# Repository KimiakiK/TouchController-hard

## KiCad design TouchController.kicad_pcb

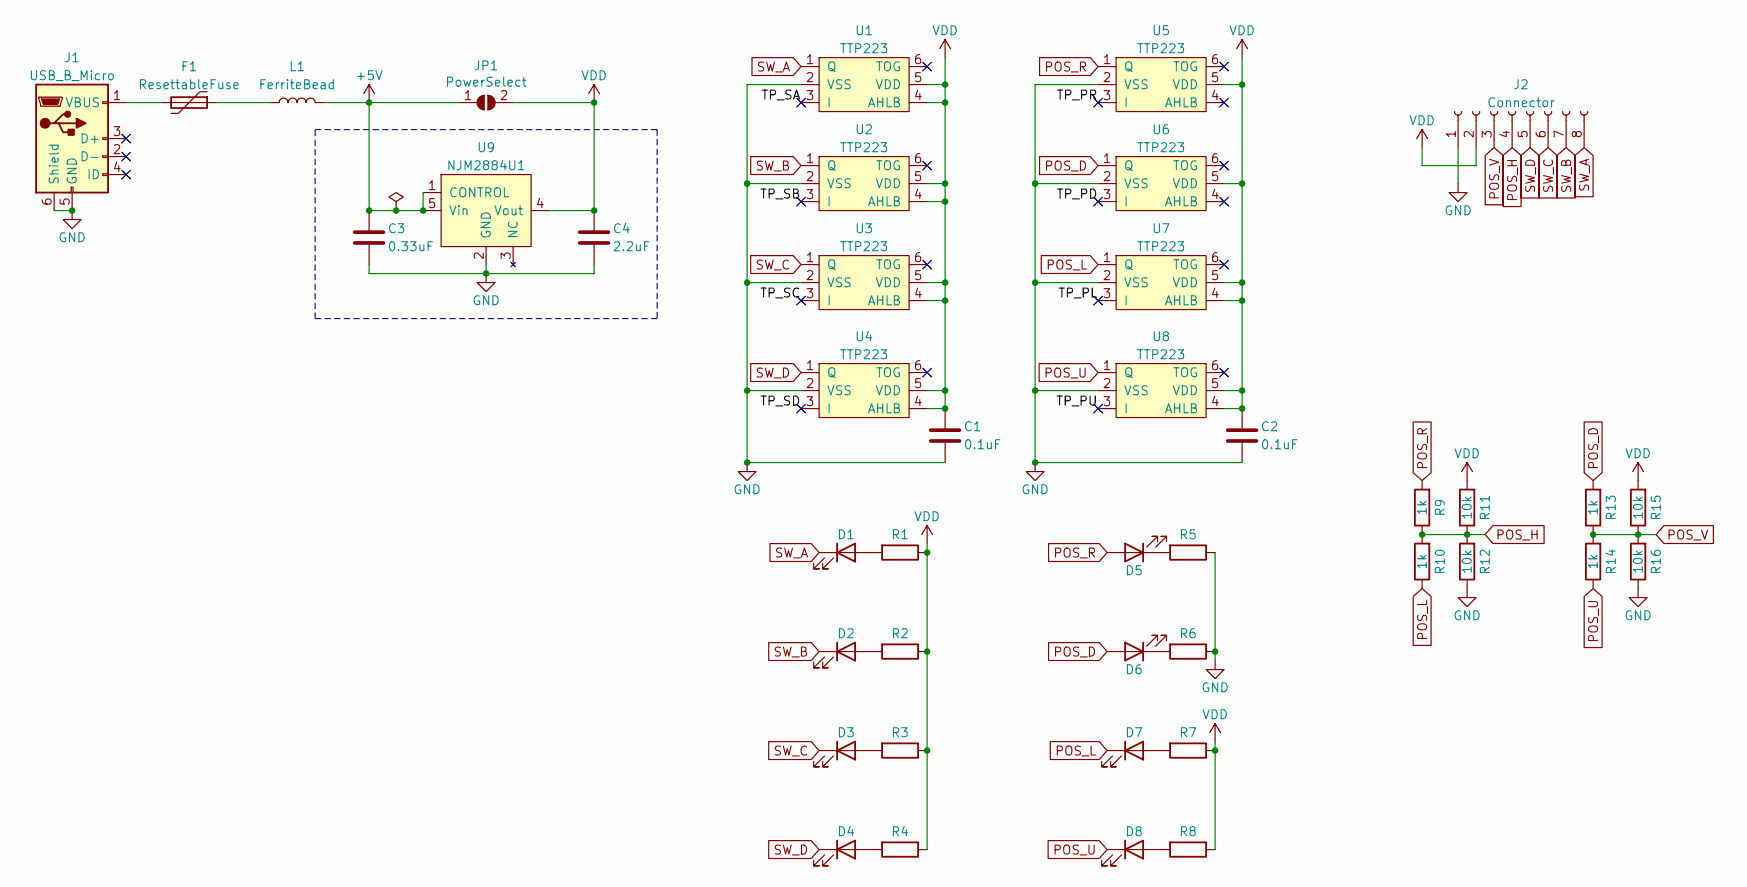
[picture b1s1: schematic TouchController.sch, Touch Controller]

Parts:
C1, C2: 0.1uF; 1608Metric
C3: 0.33uF; 1608Metric
C4: 2.2uF; 1608Metric
D1, D2, D3, D4, D5, D6, D7, D8: LED; 1608_LED
F1: ResettableFuse; 1608Metric
J1: USB_B_Micro; ZX62-B-5PA
J2: Connector; PinSocket_1x08_P2.54mm_Vertical
JP1: PowerSelect; SolderJumper-2_P1.3mm_Open_RoundedPad1.0x1.5mm
L1: FerriteBead; 1608Metric
R1, R2, R3, R4, R5, R6, R7, R8: R; 1608Metric
R9, R10, R13, R14: 1k; 1608Metric
R11, R12, R15, R16: 10k; 1608Metric
U1, U2, U3, U4, U5, U6, U7, U8: TTP223; SOT-23-6
U9: NJM2884U1; SOT-89-5

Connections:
+5V: C3.1, JP1.1 (A), L1.2, U9.1 (CONTROL), U9.5 (Vin)
/TP_PD: U6.3 (I)
/TP_PL: U7.3 (I)
/TP_PR: U5.3 (I)
/TP_PU: U8.3 (I)
/TP_SA: U1.3 (I)
/TP_SB: U2.3 (I)
/TP_SC: U3.3 (I)
/TP_SD: U4.3 (I)
GND: C1.2, C2.2, C3.2, C4.2, J1.5 (GND), J1.6 (Shield), J2.1, R5.1, R6.1, R12.1, R16.1, U1.2 (VSS), U2.2 (VSS), U3.2 (VSS), U4.2 (VSS), U5.2 (VSS), U6.2 (VSS), U7.2 (VSS), U8.2 (VSS), U9.2 (GND)
unnamed: D1.2 (A), R1.2
unnamed: D2.2 (A), R2.2
unnamed: D3.2 (A), R3.2
unnamed: D4.2 (A), R4.2
unnamed: D5.1 (K), R5.2
unnamed: D6.1 (K), R6.2
unnamed: D7.2 (A), R7.2
unnamed: D8.2 (A), R8.2
unnamed: F1.1, L1.1
unnamed: F1.2, J1.1 (VBUS)
POS_D: D6.2 (A), R13.2, U6.1 (Q)
POS_H: J2.4, R9.1, R10.2, R11.1, R12.2
POS_L: D7.1 (K), R10.1, U7.1 (Q)
POS_R: D5.2 (A), R9.2, U5.1 (Q)
POS_U: D8.1 (K), R14.1, U8.1 (Q)
POS_V: J2.3, R13.1, R14.2, R15.1, R16.2
SW_A: D1.1 (K), J2.8, U1.1 (Q)
SW_B: D2.1 (K), J2.7, U2.1 (Q)
SW_C: D3.1 (K), J2.6, U3.1 (Q)
SW_D: D4.1 (K), J2.5, U4.1 (Q)
VDD: C1.1, C2.1, C4.1, J2.2, JP1.2 (B), R1.1, R2.1, R3.1, R4.1, R7.1, R8.1, R11.2, R15.2, U1.4 (AHLB), U1.5 (VDD), U2.4 (AHLB), U2.5 (VDD), U3.4 (AHLB), U3.5 (VDD), U4.4 (AHLB), U4.5 (VDD), U5.5 (VDD), U6.5 (VDD), U7.4 (AHLB), U7.5 (VDD), U8.4 (AHLB), U8.5 (VDD), U9.4 (Vout)

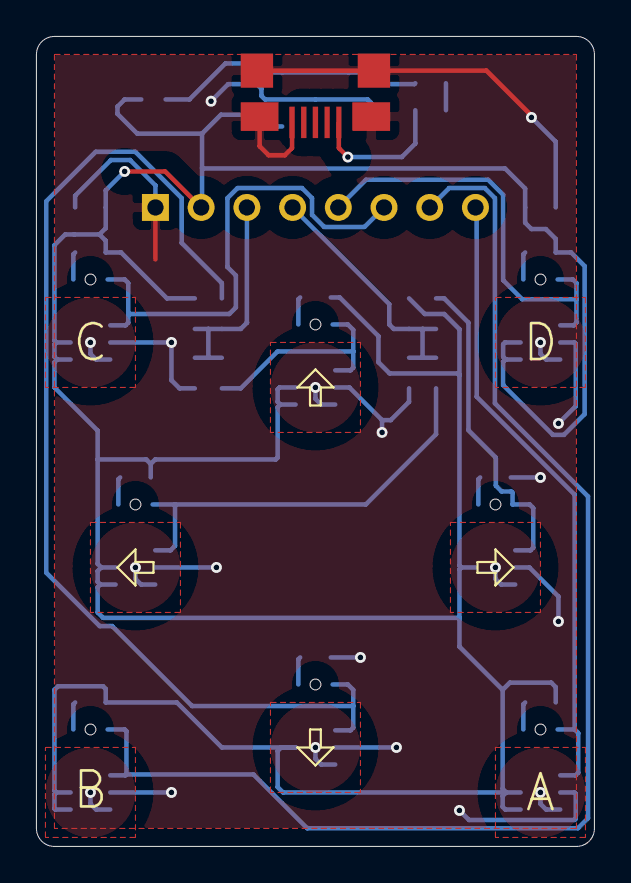
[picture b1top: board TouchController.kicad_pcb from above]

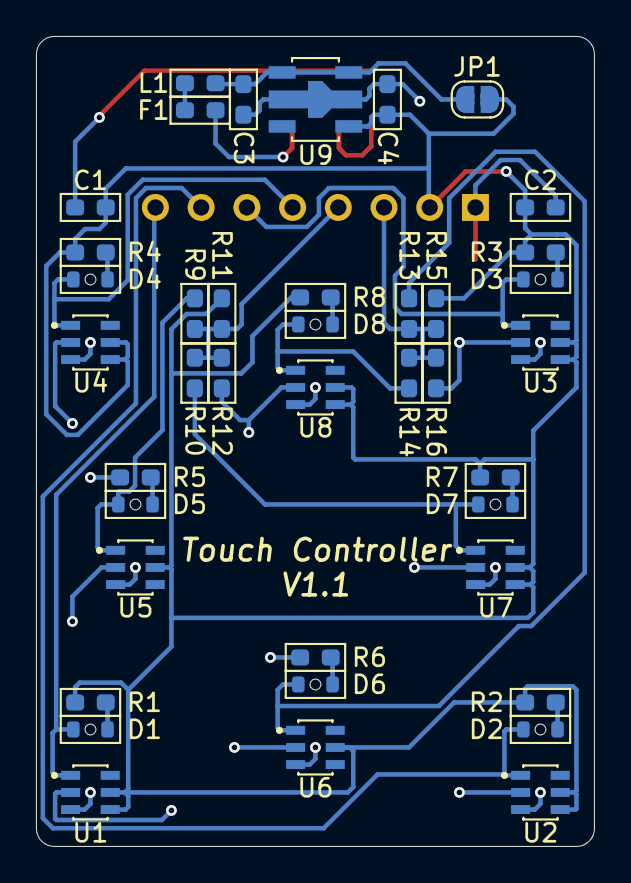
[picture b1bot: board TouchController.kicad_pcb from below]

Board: 2 copper layers, 31.0 x 45.0 mm, 42 parts (40 on the bottom side), 23 nets.

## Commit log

2021-07-10 基板 V1.0
2021-08-13 基板 V1.1
